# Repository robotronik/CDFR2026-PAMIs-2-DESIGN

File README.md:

# 🤖 PAMI - Coupe de France de Robotique 2026 - Carte Électronique (PCB)

Bienvenue sur le dépôt dédié à la conception de la carte électronique (PCB) des **PAMI** (Petits Actionneurs Mobiles Intelligents) de notre équipe pour la Coupe de France de Robotique 2026.

Ce dépôt centralise les schémas, le routage, les fichiers de fabrication (Gerber) et la nomenclature (BOM) de la carte mère du robot.

---

## ⚙️ Spécifications Matérielles (Hardware)

### ⚡ Architecture Électronique & Puissance
La carte mère est conçue autour d'un microcontrôleur ESP32 et intègre toute la distribution de puissance, le contrôle moteur et les interfaces capteurs/IHM.

* **Cerveau :** Microcontrôleur ESP32 (Modèle précis à déterminer).
* **Programmation & Debug :** Port USB-C intégré à la carte.
* **Alimentation Générale :** Entrée Batterie avec coupure de sécurité matérielle via un **Bouton d'Arrêt d'Urgence (BAU)**.
* **Drivers Moteurs DC :** 2x TB67H420FTG (Contrôle indépendant des moteurs gauche/droit).

### 🏎️ Motorisation & Cinématique (Rappel de la cible)
* **Moteurs :** 2x CHW-4632-370 ABHL 6V (Moteurs CC à balais avec réducteur à vis sans fin).
* **Rapport de réduction :** 1:32 (Renvoi d'angle à 90° - 185 RPM à vide).
* **Vitesse de croisière estimée :** ~27 cm/s (avec des roues de 40 mm).
* **Couple de décrochage (Stall Torque) :** > 2.9 Kg.cm par moteur.
* **Odométrie :** Encodeurs magnétiques à effet Hall (Quadratrure Phase A/B), offrant ~352 tics par tour de roue.

### 📡 Capteurs & Actionneurs Auxiliaires
* **Évitement (Adversaires/Obstacles) :** Interface pour capteur LIDAR.
* **Actionneurs secondaires :** Connectique pour 2x Servomoteurs.

### 🕹️ Interface Homme-Machine (IHM) intégrée
* **Affichage Équipe :** 1x LED RGB.
* **Indicateurs de Statut (Batterie, Erreurs, etc.) :** 4x LEDs standards.
* **Configuration (Changement couleur équipe) :** 1x Bouton poussoir utilisateur.

---

## 📂 Architecture du Dépôt

```text
📦 PAMI-PCB-2026
 ┣ 📂 hardware/               # Projet KiCad (Schémas et Routage)
 ┣ 📂 fabrication/            # Fichiers générés pour l'usinage/assemblage (Générés en fin de projet)
 ┣ 📂 docs/                   # Documentation technique
 ┗ 📜 README.md

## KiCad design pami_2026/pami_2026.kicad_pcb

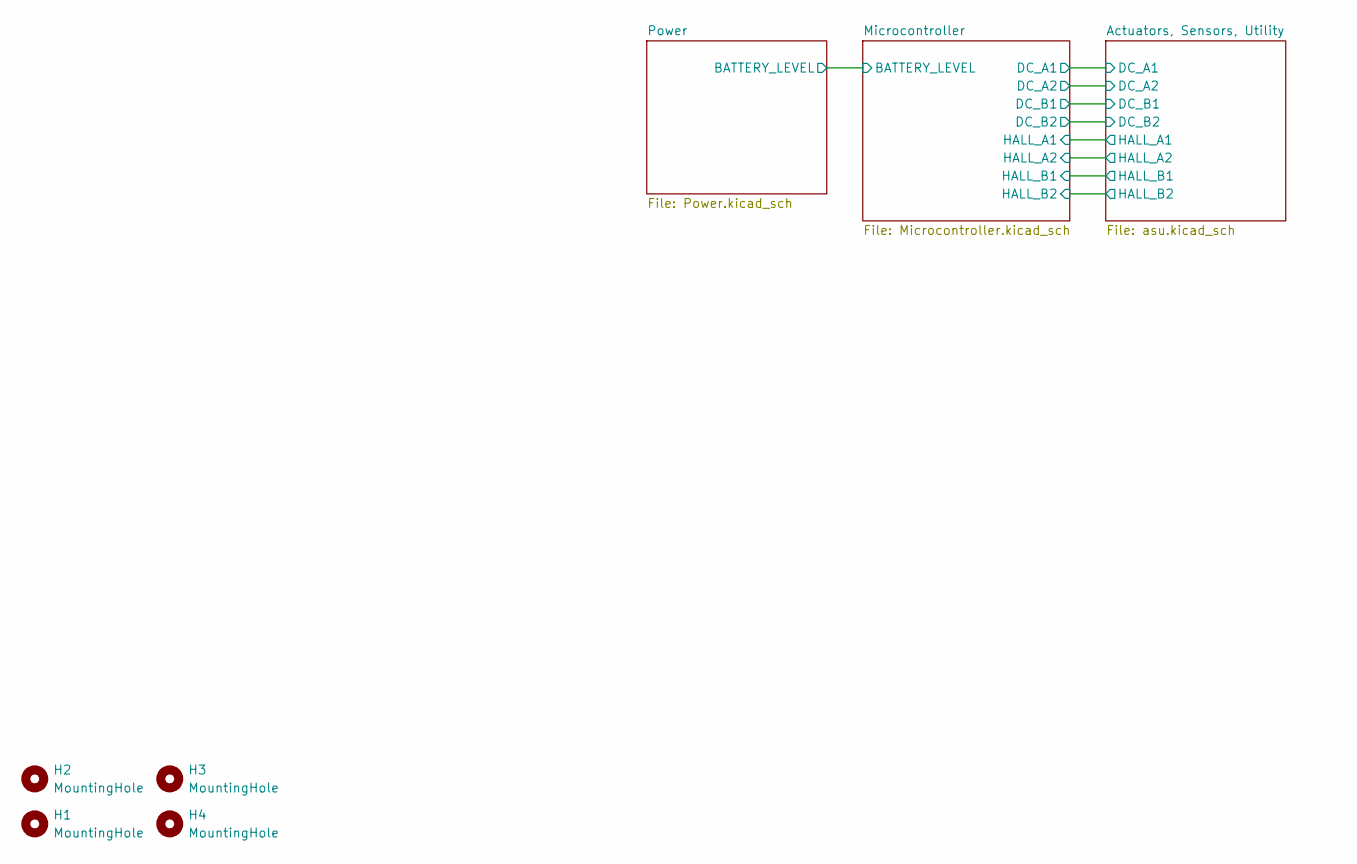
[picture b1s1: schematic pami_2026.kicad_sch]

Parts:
H1, H2, H3, H4: MountingHole; MountingHole_2.2mm_M2_ISO7380_Pad

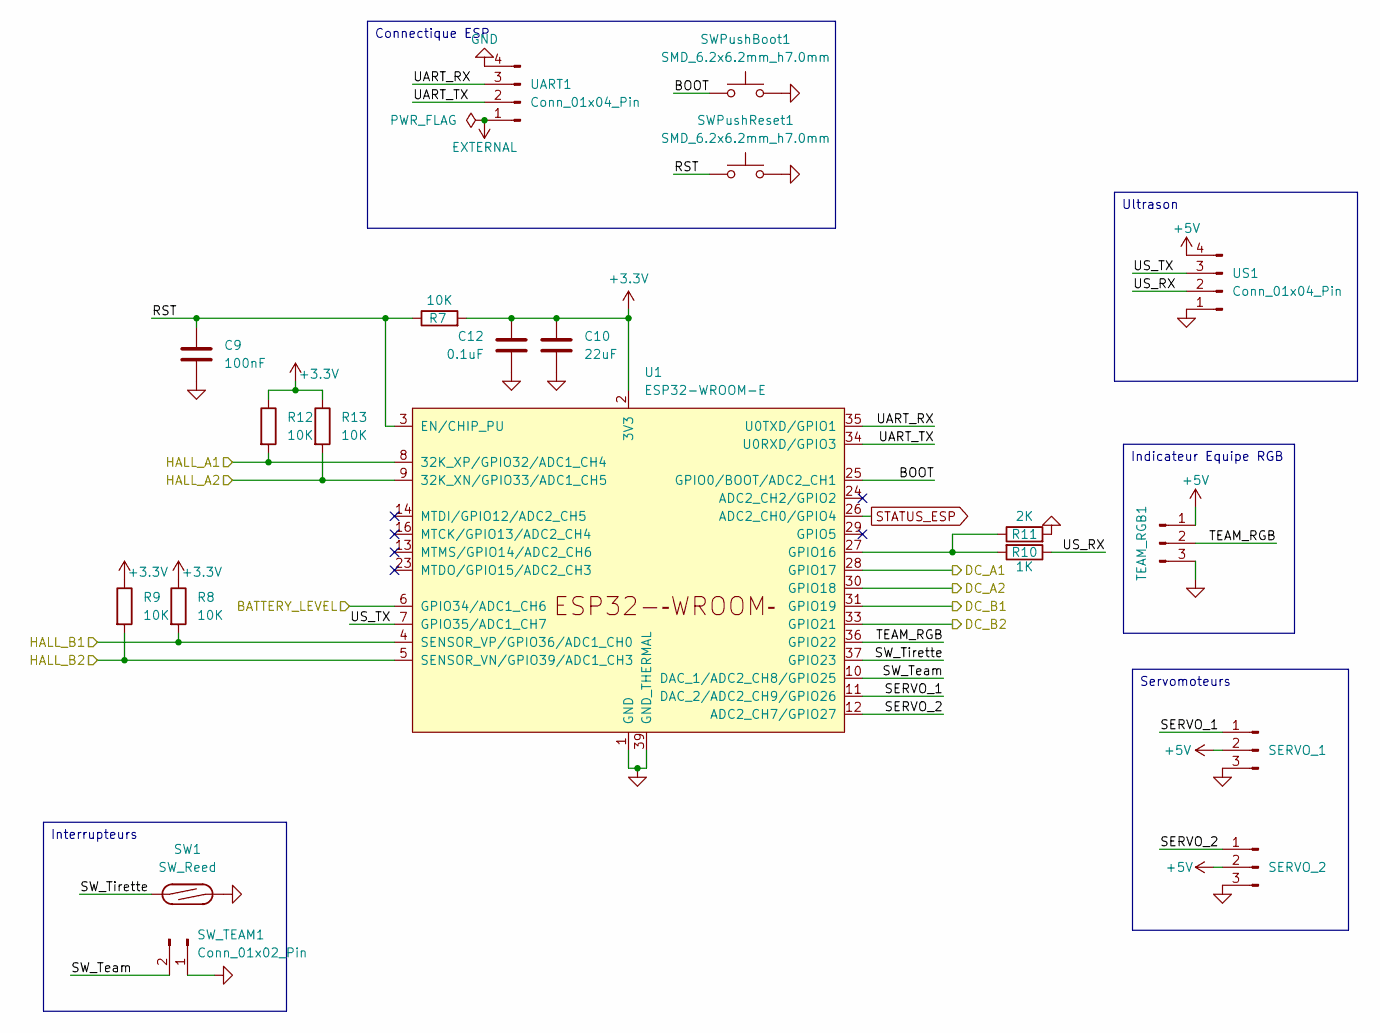
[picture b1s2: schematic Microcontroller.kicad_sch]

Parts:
C9: 100nF; C_0603_1608Metric; LCSC C1591
C10: 22uF; C_0805_2012Metric; LCSC C602037
C12: 0.1uF; C_0603_1608Metric; LCSC C1591
R7, R8, R9, R12, R13: 10K; R_0603_1608Metric; LCSC C98220
R10: 1K; R_0603_1608Metric; LCSC C22548
R11: 2K; R_0603_1608Metric; LCSC C105576
SERVO_1, SERVO_2: Conn_01x03_Pin; PinHeader_1x03_P2.54mm_Vertical; LCSC C32713269
SW1: SW_Reed; PinHeader_1x02_P2.54mm_Vertical; LCSC C32713268
SWPushBoot1: SMD_6.2x6.2mm_h7.0mm; Push_SMD_6.2x6.2mm; Mfg Part# 679-2384-2-ND; LCSC C967701
SWPushReset1: SMD_6.2x6.2mm_h7.0mm; Push_SMD_6.2x6.2mm; Mfg Part# 679-2384-2-ND; LCSC C967701
SW_TEAM1: Conn_01x02_Pin; PinHeader_1x02_P2.54mm_Vertical; LCSC C32713268
TEAM_RGB1: Conn_01x03_Pin; PinHeader_1x03_P2.54mm_Vertical; LCSC C32713269
U1: ESP32-WROOM-E; ESP32-WROOM-32E; LCSC C701343
UART1: Conn_01x04_Pin; PinHeader_1x04_P2.54mm_Vertical; LCSC C42431808
US1: Conn_01x04_Pin; PinHeader_1x04_P2.54mm_Vertical; LCSC C42431808

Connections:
+3.3V: C10.1, C12.1, R7.2, R8.1, R9.1, R12.1, R13.1, U1.2 (3V3); also elsewhere on the board
+5V: SERVO_1.2, SERVO_2.2, TEAM_RGB1.1, US1.4; also elsewhere on the board
/Actuators, Sensors, Utility/DC_A1: U1.28 (GPIO17); also elsewhere on the board
/Actuators, Sensors, Utility/DC_A2: U1.30 (GPIO18); also elsewhere on the board
/Actuators, Sensors, Utility/DC_B1: U1.31 (GPIO19); also elsewhere on the board
/Actuators, Sensors, Utility/DC_B2: U1.33 (GPIO21); also elsewhere on the board
/Actuators, Sensors, Utility/HALL_A1: R12.2, U1.8 (32K_XP/GPIO32/ADC1_CH4); also elsewhere on the board
/Actuators, Sensors, Utility/HALL_A2: R13.2, U1.9 (32K_XN/GPIO33/ADC1_CH5); also elsewhere on the board
/Actuators, Sensors, Utility/HALL_B1: R8.2, U1.4 (SENSOR_VP/GPIO36/ADC1_CH0); also elsewhere on the board
/Actuators, Sensors, Utility/HALL_B2: R9.2, U1.5 (SENSOR_VN/GPIO39/ADC1_CH3); also elsewhere on the board
/Microcontroller/BATTERY_LEVEL: U1.6 (GPIO34/ADC1_CH6); also elsewhere on the board
/Microcontroller/BOOT: SWPushBoot1.1, U1.25 (GPIO0/BOOT/ADC2_CH1)
/Microcontroller/RST: C9.1, R7.1, SWPushReset1.1, U1.3 (EN/CHIP_PU)
/Microcontroller/SERVO_1: SERVO_1.1, U1.11 (DAC_2/ADC2_CH9/GPIO26)
/Microcontroller/SERVO_2: SERVO_2.1, U1.12 (ADC2_CH7/GPIO27)
/Microcontroller/SW_Team: SW_TEAM1.2, U1.10 (DAC_1/ADC2_CH8/GPIO25)
/Microcontroller/SW_Tirette: SW1.1, U1.37 (GPIO23)
/Microcontroller/TEAM_RGB: TEAM_RGB1.2, U1.36 (GPIO22)
/Microcontroller/UART_RX: U1.35 (U0TXD/GPIO1), UART1.3
/Microcontroller/UART_TX: U1.34 (U0RXD/GPIO3), UART1.2
/Microcontroller/US_RX: R10.1, US1.2
/Microcontroller/US_TX: U1.7 (GPIO35/ADC1_CH7), US1.3
EXTERNAL: UART1.1; also elsewhere on the board
GND: C9.2, C10.2, C12.2, R11.2, SERVO_1.3, SERVO_2.3, SW1.2, SWPushBoot1.2, SWPushReset1.2, SW_TEAM1.1, TEAM_RGB1.3, U1.1 (GND), U1.15 (GND), U1.38 (GND), U1.39 (GND_THERMAL), UART1.4, US1.1; also elsewhere on the board
unnamed: R10.2, R11.1, U1.27 (GPIO16)
STATUS_ESP: U1.26 (ADC2_CH0/GPIO4); also elsewhere on the board

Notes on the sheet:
Interrupteurs
Indicateur Equipe RGB
Connectique ESP
Servomoteurs
Ultrason

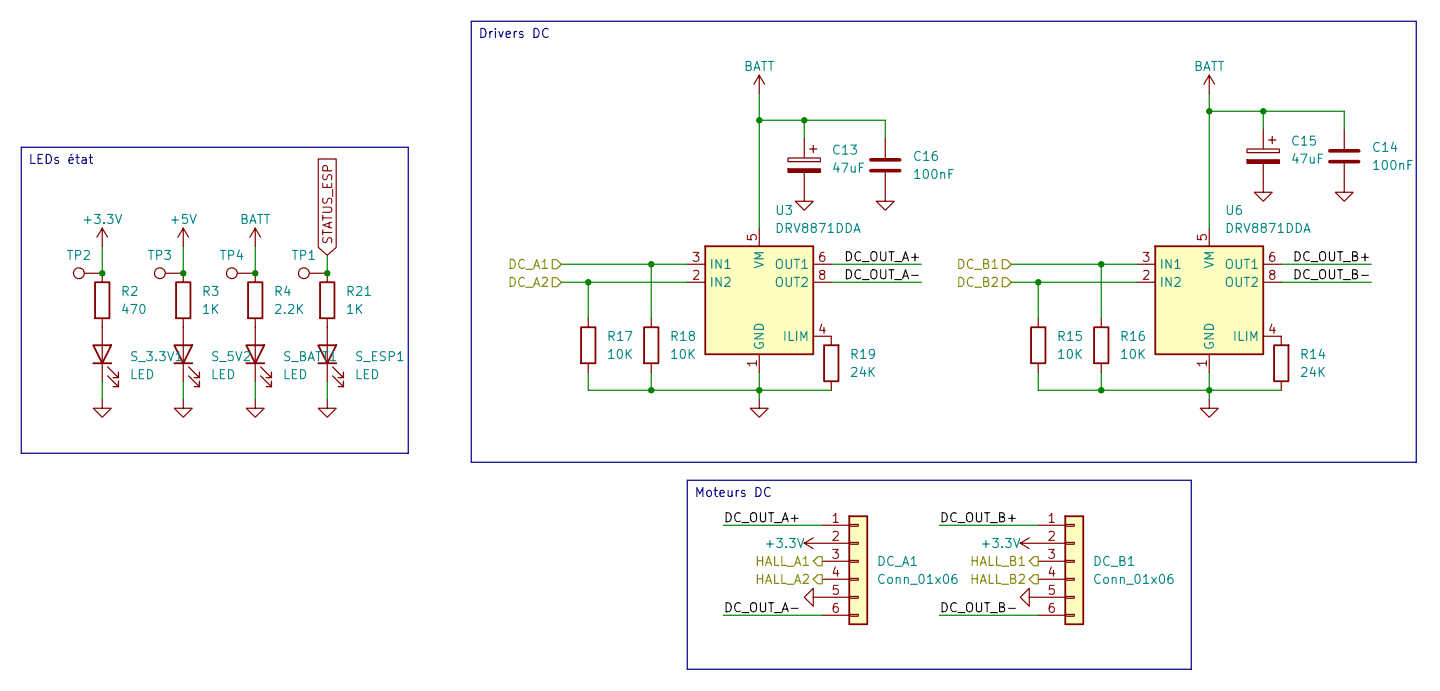
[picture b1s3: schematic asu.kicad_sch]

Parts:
C13, C15: 47uF; Panasonic_F; LCSC C128464
C14, C16: 100nF; C_0603_1608Metric; LCSC C1591
DC_A1: Conn_01x06; PinHeader_1x06_P2.54mm_Vertical; LCSC C37208
DC_B1: Conn_01x06; PinHeader_1x06_P2.54mm_Vertical; LCSC C37208
R2: 470; R_0603_1608Metric; LCSC C4045076
R3, R21: 1K; R_0603_1608Metric; LCSC C22548
R4: 2.2K; R_0603_1608Metric; LCSC C114662
R14, R19: 24K; R_0603_1608Metric; LCSC C2930081
R15, R16, R17, R18: 10K; R_0603_1608Metric; LCSC C98220
S_3.3V1, S_5V2: LED; LED_0603_1608Metric; LCSC C965799
S_BATT1: LED; LED_0603_1608Metric; LCSC C965799
S_ESP1: LED; LED_0603_1608Metric; LCSC C965799
TP1, TP2, TP3, TP4: TestPoint; TestPoint_Pad_1.0x1.0mm
U3, U6: DRV8871DDA; Texas_HTSOP-8-1EP_3.9x4.9mm_P1.27mm_EP2.95x4.9mm_Mask2.4x3.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; LCSC C701805

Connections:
+3.3V: DC_A1.2, DC_B1.2, R2.1, TP2.1; also elsewhere on the board
+5V: R3.1, TP3.1; also elsewhere on the board
/Actuators, Sensors, Utility/DC_A1: R18.1, U3.3 (IN1); also elsewhere on the board
/Actuators, Sensors, Utility/DC_A2: R17.1, U3.2 (IN2); also elsewhere on the board
/Actuators, Sensors, Utility/DC_B1: R16.1, U6.3 (IN1); also elsewhere on the board
/Actuators, Sensors, Utility/DC_B2: R15.1, U6.2 (IN2); also elsewhere on the board
/Actuators, Sensors, Utility/DC_OUT_A+: DC_A1.1, U3.6 (OUT1)
/Actuators, Sensors, Utility/DC_OUT_A-: DC_A1.6, U3.8 (OUT2)
/Actuators, Sensors, Utility/DC_OUT_B+: DC_B1.1, U6.6 (OUT1)
/Actuators, Sensors, Utility/DC_OUT_B-: DC_B1.6, U6.8 (OUT2)
/Actuators, Sensors, Utility/HALL_A1: DC_A1.3; also elsewhere on the board
/Actuators, Sensors, Utility/HALL_A2: DC_A1.4; also elsewhere on the board
/Actuators, Sensors, Utility/HALL_B1: DC_B1.3; also elsewhere on the board
/Actuators, Sensors, Utility/HALL_B2: DC_B1.4; also elsewhere on the board
BATT: C13.1, C14.1, C15.1, C16.1, R4.1, TP4.1, U3.5 (VM), U6.5 (VM); also elsewhere on the board
GND: C13.2, C14.2, C15.2, C16.2, DC_A1.5, DC_B1.5, R14.1, R15.2, R16.2, R17.2, R18.2, R19.1, S_3.3V1.1 (K), S_5V2.1 (K), S_BATT1.1 (K), S_ESP1.1 (K), U3.1 (GND), U3.7 (GND), U3.9 (GND), U6.1 (GND), U6.7 (GND), U6.9 (GND); also elsewhere on the board
unnamed: R2.2, S_3.3V1.2 (A)
unnamed: R3.2, S_5V2.2 (A)
unnamed: R4.2, S_BATT1.2 (A)
unnamed: R21.2, S_ESP1.2 (A)
unnamed: R19.2, U3.4 (ILIM)
unnamed: R14.2, U6.4 (ILIM)
STATUS_ESP: R21.1, TP1.1; also elsewhere on the board

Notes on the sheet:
Moteurs DC
LEDs état
Drivers DC

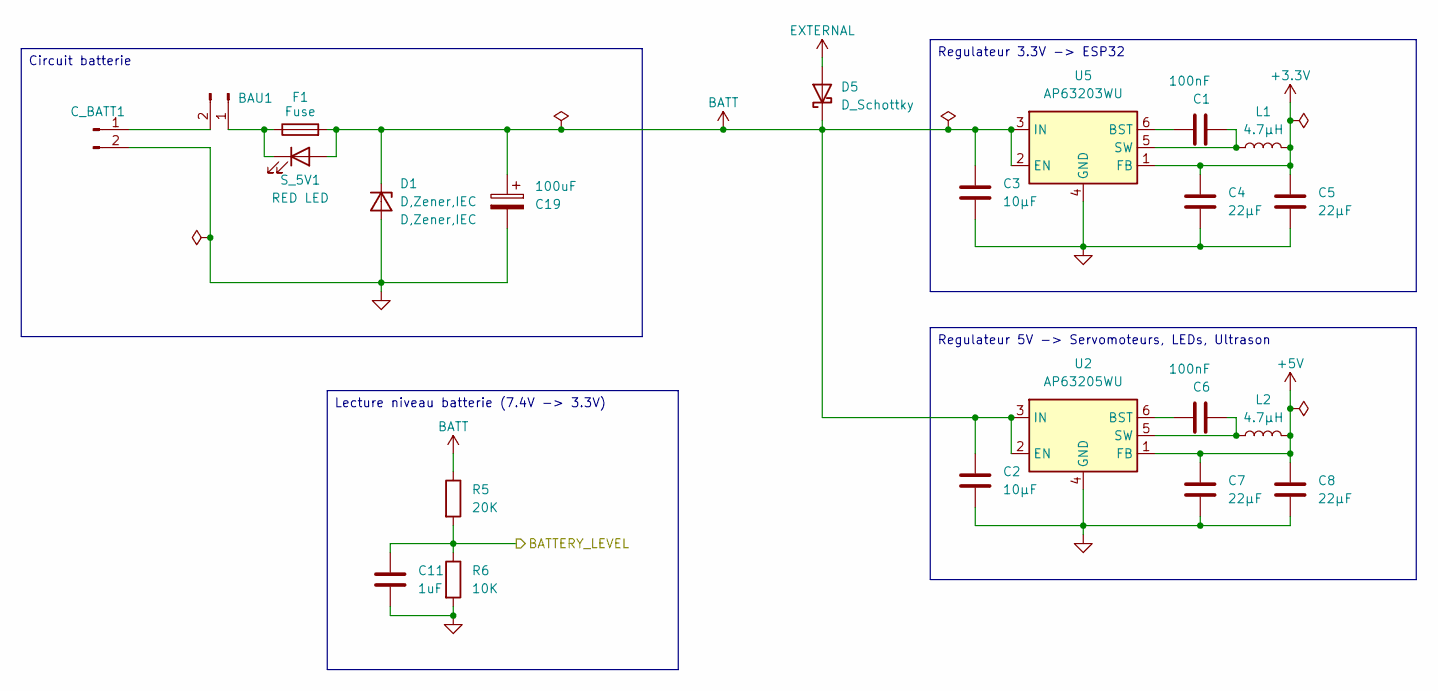
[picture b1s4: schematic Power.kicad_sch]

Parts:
BAU1: Conn_01x02_Pin; PinHeader_1x02_P2.54mm_Vertical; LCSC C32713268
C1, C6: 100nF; C_0603_1608Metric; LCSC C1591
C2, C3: 10µF; C_0805_2012Metric; LCSC C15850
C4, C5, C7, C8: 22µF; C_0805_2012Metric; LCSC C602037
C11: 1uF; C_0603_1608Metric; LCSC C15849
C19: 100uF; CAP_EEETC1C101V; LCSC C2163886
C_BATT1: Conn_01x02_Pin; PinHeader_1x02_P2.54mm_Vertical; LCSC C32713268
D1: D,Zener,IEC; D_SOD-123; LCSC C41408110
D5: D_Schottky; D_SOD-123; LCSC C908229
F1: Fuse; Fuse_1206_3216Metric; LCSC C48783168
L1, L2: 4.7µH; L_Wurth_WE-LQSH-4020; LCSC C6364810
R5: 20K; R_0603_1608Metric; LCSC C105575
R6: 10K; R_0603_1608Metric; LCSC C98220
S_5V1: RED LED; LED_0603_1608Metric; LCSC C965799
U2: AP63205WU; TSOT-23-6; LCSC C2071056
U5: AP63203WU; TSOT-23-6; LCSC C780769

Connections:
+3.3V: C4.1, C5.1, L1.2, U5.1 (FB); also elsewhere on the board
+5V: C7.1, C8.1, L2.2, U2.1 (FB); also elsewhere on the board
/Microcontroller/BATTERY_LEVEL: C11.1, R5.2, R6.1; also elsewhere on the board
BATT: C2.1, C3.1, C19.1, D1.1 (K-), D5.1 (K), F1.2, R5.1, S_5V1.2 (A), U2.2 (EN), U2.3 (IN), U5.2 (EN), U5.3 (IN); also elsewhere on the board
EXTERNAL: D5.2 (A); also elsewhere on the board
GND: C2.2, C3.2, C4.2, C5.2, C7.2, C8.2, C11.2, C19.2, C_BATT1.2, D1.2 (A+), R6.2, U2.4 (GND), U5.4 (GND); also elsewhere on the board
unnamed: BAU1.1, F1.1, S_5V1.1 (K)
unnamed: BAU1.2, C_BATT1.1
unnamed: C6.1, U2.6 (BST)
unnamed: C6.2, L2.1, U2.5 (SW)
unnamed: C1.1, U5.6 (BST)
unnamed: C1.2, L1.1, U5.5 (SW)

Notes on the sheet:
Regulateur 5V -> Servomoteurs, LEDs, Ultrason
Circuit batterie
Regulateur 3.3V -> ESP32
Lecture niveau batterie (7.4V -> 3.3V)

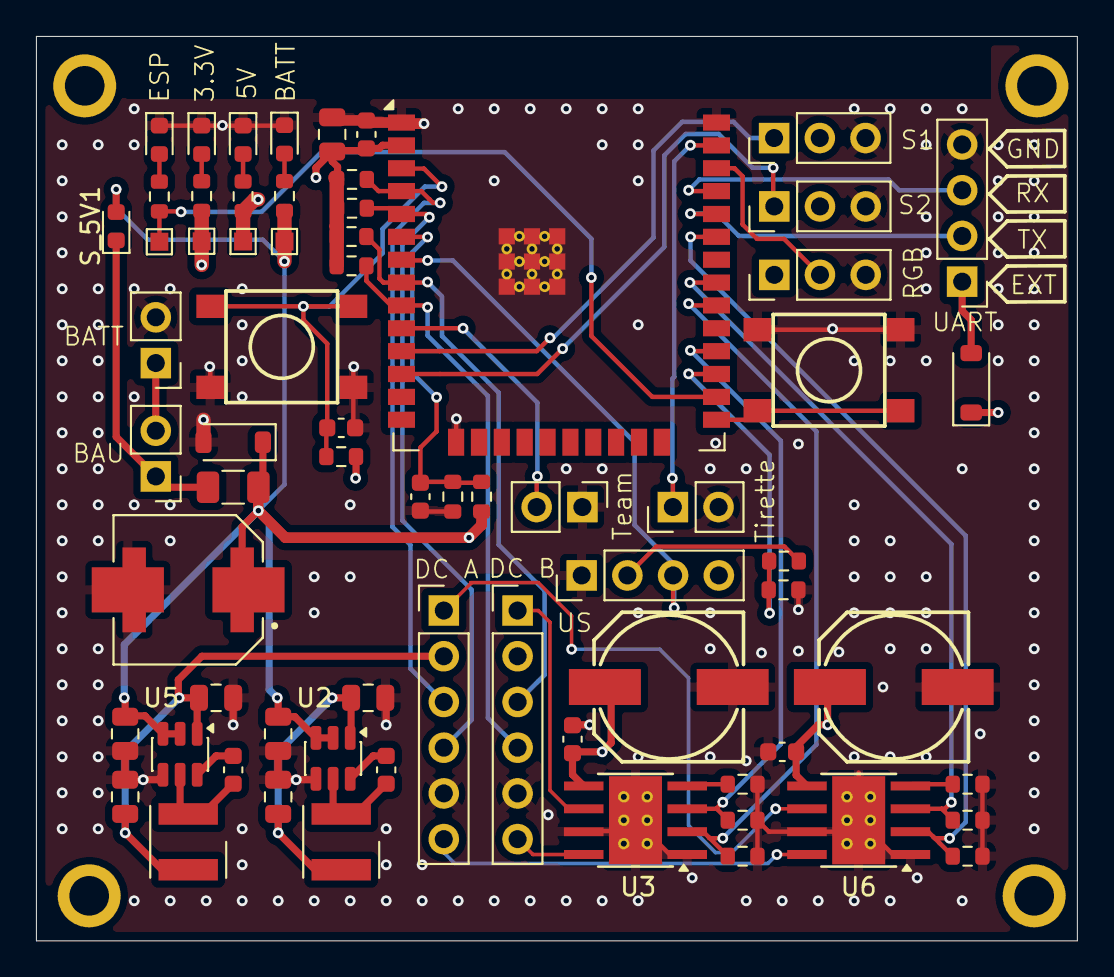
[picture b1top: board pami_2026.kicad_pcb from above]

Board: 4 copper layers, 57.8 x 50.2 mm, 72 parts (0 on the bottom side), 43 nets.

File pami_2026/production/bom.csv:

Designator,Footprint,Quantity,Value,LCSC Part #
"BAU1, C_BATT1, SW_TEAM1",PinHeader_1x02_P2.54mm_Vertical,3,Conn_01x02_Pin,C32713268
"C1, C14, C16, C6, C9",0603,5,100nF,C1591
C10,0805,1,22uF,C602037
C11,0603,1,1uF,C15849
C12,0603,1,0.1uF,C1591
"C13, C15",Panasonic_F,2,47uF,C128464
C19,CAP_EEETC1C101V,1,100uF,C2163886
"C2, C3",0805,2,10µF,C15850
"C4, C5, C7, C8",0805,4,22µF,C602037
D1,D_SOD-123,1,"D,Zener,IEC",C41408110
D5,D_SOD-123,1,D_Schottky,C908229
"DC_A1, DC_B1",PinHeader_1x06_P2.54mm_Vertical,2,Conn_01x06,C37208
F1,1206,1,Fuse,C48783168
"L1, L2",L_Wurth_WE-LQSH-4020,2,4.7µH,C6364810
"Q1, Q2",SOT-223,2,PMOS,C49066897
R1,0603,1,100K,C2906980
"R10, R21, R3",0603,3,1K,C22548
R11,0603,1,2K,C105576
"R12, R13, R15, R16, R17, R18, R20, R6, R7, R8, R9",0603,11,10K,C98220
"R14, R19",0603,2,24K,C2930081
R2,0603,1,470,C4045076
R4,0603,1,2.2K,C114662
R5,0603,1,20K,C105575
"SERVO_1, SERVO_2, TEAM_RGB1",PinHeader_1x03_P2.54mm_Vertical,3,Conn_01x03_Pin,C32713269
SW1,PinHeader_1x02_P2.54mm_Vertical,1,SW_Reed,C32713268
"SWPUSHBOOT1, SWPUSHRESET1",Push_SMD_6.2x6.2mm,2,SMD_6.2x6.2mm_h7.0mm,C967701
"S_3.3V1, S_5V1, S_BATT1, S_ESP1",0603,4,LED,C965799
U1,ESP32-WROOM-32E,1,ESP32-WROOM-E,C701343
U2,TSOT-23-6,1,AP63205WU,C2071056
"U3, U6",Texas_HTSOP-8-1EP_3.9x4.9mm_P1.27mm_EP2.95x4.9mm_Mask2.4x3.1mm_ThermalVias,2,DRV8871DDA,C701805
U5,TSOT-23-6,1,AP63203WU,C780769
"UART1, US1",PinHeader_1x04_P2.54mm_Vertical,2,Conn_01x04_Pin,C42431808

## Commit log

2026-03-05 [INIT]
2026-03-10 gitignore
2026-03-10 voltage regulators
2026-03-10 Battery circuit and DC Driver
2026-03-10 WIP alim stage
2026-03-11 WIP actuators
2026-03-11 WIP USB programmer
2026-03-12 Change DC drivers, apply datasheet recommendations, add big capacitor, remove USB programmer for simple connector
2026-03-12 Hall pull up
2026-03-12 Ultrason, empreintes et petites corrections
2026-03-12 Fix polarity protection and change drivers
2026-03-12 update caps
2026-03-12 footprints
2026-03-12 make erc happier
2026-03-13 Fix: ERC is Happy - proper footprints - Feat: add multiplexer for external power
2026-03-13 fix footprints
2026-03-13 fix strapping pin
2026-03-14 FEAT : Routing
2026-03-14 FEAT : Via Stitching
2026-03-16 Feat: mounting holes, indications, fix capa polarity
2026-03-17 Feat: BOM LCSC + big plan de masse
2026-04-19 Cleanup
2026-04-20 Fixes and updates to v2
2026-04-21 Fix servo pinout
